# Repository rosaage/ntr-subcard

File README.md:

# ntr-subcard
Clone of NTR eeprom subcard

For eeprom/flash selection: https://gbatemp.net/threads/ds-cartridge-replacement-save-chips.646745/

Connector: [Molex SlimStack 2x20 P0.50mm - 53748-0408](https://www.digikey.com/en/products/detail/molex/0537480408/1059857)

# Changes
At least when looking on aliexpress a wide version of U2 is a lot more common and cheap, so I extended the footprint to support `M45PE40-VMW6TG` (4 Mbit Flash) and similar chips.

# Production 512 kbit eeprom
A finished PCB can be ordered from JLCPCB by uploading the `Gerbers.zip` file and checking the PCB Assembly option.
`BOM.csv` and `CPL.csv` will need to be uploaded for the assembly. This is set to use U1 as a 512 kbit eeprom chip, as this version was cheap and in stock at jlcpcb.
By modifiying `BOM.csv` before uploading a different part can be selected (also possible on the website after uploading).
It is also possible to order it with only the connector and passives and solder on U1 or U2 manually.

# Production 2/4 Mbit Flash
I have not looked into a suitable part for U2 from JLCPCB, but I made CPL files for the coordinates for both wide and slim variants:
* Wide 208 mil: `CPL-U2-wide.csv`
* Slim 150 mil: `CPL-U2-slim.csv`

# Finished boards from JLCPCB

# Future revisions
While I don't have any plans to make a new revision right now I have some things I would like to add.
By moving the CE pins from flash/eeprom to a SPDT switch and adding a second pull-up it would be possible
to have one card with both eeprom and flash at the same time. A set of solder bridge pads or pads for 0-ohm resistors would also be a quick option if no suitable switch can be sourced.

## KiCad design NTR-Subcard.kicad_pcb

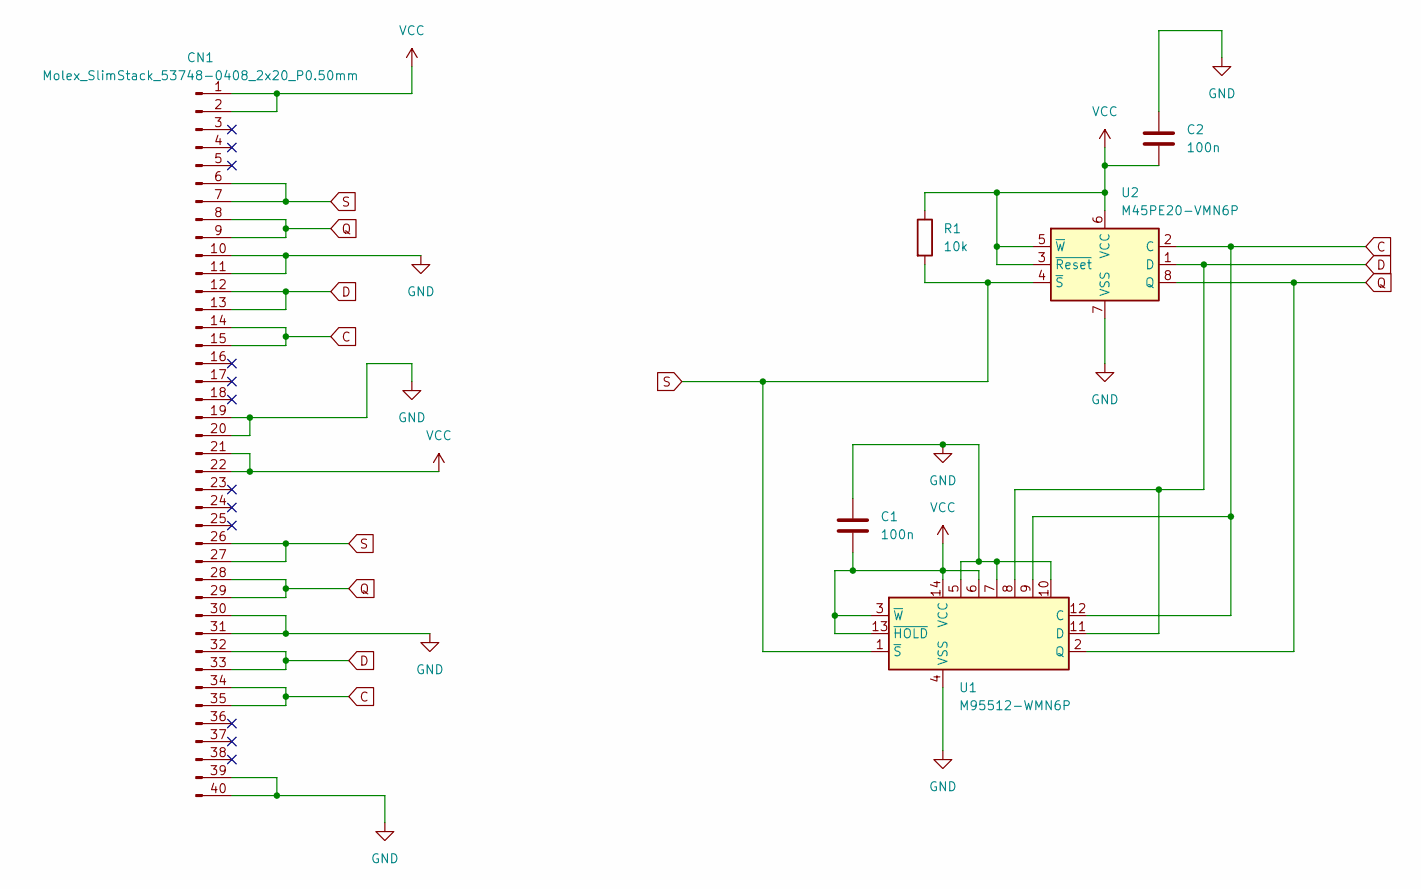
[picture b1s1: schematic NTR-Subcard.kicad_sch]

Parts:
C1, C2: 100n; C_0603_1608Metric_Pad1.08x0.95mm_HandSolder
CN1: Molex_SlimStack_53748-0408_2x20_P0.50mm; Molex_SlimStack_53748-0408_2x20_P0.50mm_Vertical-tage
R1: 10k; R_0603_1608Metric_Pad0.98x0.95mm_HandSolder
U1: M95512-WMN6P; TSSOP-14_4.4x5mm_P0.65mm
U2: M45PE20-VMN6P; SOIC-8_3.9x3.9-7.62mm_P1.27mm

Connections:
C: CN1.14, CN1.15, CN1.34, CN1.35, U1.9, U1.12 (C), U2.2 (C)
D: CN1.12, CN1.13, CN1.32, CN1.33, U1.8, U1.11 (D), U2.1 (D)
GND: C1.1, C2.1, CN1.10, CN1.11, CN1.19, CN1.20, CN1.30, CN1.31, CN1.39, CN1.40, U1.4 (VSS), U1.5, U1.7, U1.10, U2.7 (VSS)
Q: CN1.8, CN1.9, CN1.28, CN1.29, U1.2 (Q), U2.8 (Q)
S: CN1.6, CN1.7, CN1.26, CN1.27, R1.2, U1.1 (~S), U2.4 (~S)
VCC: C1.2, C2.2, CN1.1, CN1.2, CN1.21, CN1.22, R1.1, U1.3 (~W), U1.6, U1.13 (~HOLD), U1.14 (VCC), U2.3 (~Reset), U2.5 (~W), U2.6 (VCC)

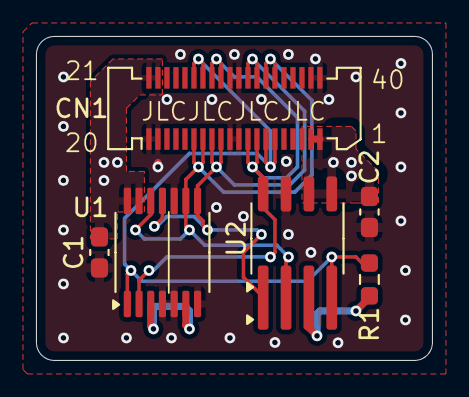
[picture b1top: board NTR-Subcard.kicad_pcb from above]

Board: 2 copper layers, 22.0 x 18.0 mm, 6 parts (0 on the bottom side), 6 nets.

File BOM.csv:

"Comment","Designator","Footprint","LCSC Part Number"
"100n","C1,C2","0603","C14663"
"Molex_SlimStack_53748-0408","CN1","53748-0408","C564064"
"10k","R1","0603","C25804"
"M95512-RDW6TP","U1","TSSOP-8","C122886"

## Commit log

2024-11-21 First version
2024-11-21 Update README.md
    Added link to parts
2024-11-21 Rename CN1, add pdf file
2025-06-17 Updates after first production batch
2025-06-17 Update README.md
    Next revision info
